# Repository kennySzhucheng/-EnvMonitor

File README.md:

# EnvMonitor — 智能环境监测站

> STM32F103C8T6 + FreeRTOS + ESP8266 桌面环境监测终端 | 练习项目

一个从零开始搭建的嵌入式 IoT 项目：裸机固件 → FreeRTOS 重构 → KiCad 画板 → 嘉立创打样，走完嵌入式产品全流程。

---

## 📸 实物展示

> ⏳ PCB 已下单，等待到货焊接后补图。

---

## ✨ 功能

| 模块 | 作用 |
|------|------|
| 🌡️ **DHT22** | 温湿度传感器，单总线(1-Wire)通信，精度 ±0.5°C / ±2%RH，挂在 PA0 上 |
| ☀️ **BH1750** | 环境光强度传感器，I²C 接口，0~65535 lux 量程，和 OLED 共用 PB6/PB7 |
| 📏 **HC-SR04** | 超声波测距模块，探测前方物体距离，用于"有人靠近"检测，PB0 发触发信号、PB1 输入捕获回波 |
| 🖥️ **OLED SSD1306** | 0.96 寸 I²C 显示屏，5 页菜单循环切换(温湿度/光照/距离/WiFi/系统信息) |
| 📡 **ESP8266-01S** | WiFi 模块，通过 UART1(PA9/PA10) 走 AT 指令，HTTP GET 方式每 60s 上传一次 ThingSpeak |
| 🚨 **三色 LED** | 红色(高温>35°C)、黄色(湿度<30%)、绿色(有人靠近<30cm)，分别接 PB12/13/14 |
| 🔔 **蜂鸣器** | 5V 有源模块，出现报警条件时由 BuzzerTask 队列驱动蜂鸣 |
| 🎛️ **三按键** | KEY1 页面切换 / KEY2 确认 / KEY3 返回，PA4/5/6，消抖电容 + 10kΩ 外部上拉 |
| ⏱️ **FreeRTOS** | 6 个任务抢占式调度，3 个互斥量保护共享资源，2 条队列做任务间通信 |
| 🛡️ **自定义 PCB** | KiCad 10 设计，80×60mm 双面板，全插件 27 元件，双面 GND 铺铜 |

---

## 🧱 硬件架构

```
                    ┌──────────────────────────────────┐
                    │        STM32F103C8T6 (72MHz)     │
                    │           Blue Pill 核心板         │
                    │                                  │
    DHT22 ──────────┤ PA0 (1-Wire)                     │
    KEY1~3 ─────────┤ PA4/PA5/PA6 (GPIO Input)        │
    ESP8266 ────────┤ PA9/PA10 (USART1, 115200bps)     │
    HC-SR04 ────────┤ PB0(Trig) / PB1(Echo, TIM3_CH4) │
    OLED+BH1750 ────┤ PB6/PB7 (I2C1, 共用总线)          │
    LED_R/Y/G ──────┤ PB12/PB13/PB14 (GPIO Output)     │
    Buzzer ─────────┤ PB15 (GPIO Output, 直连模块IO)    │
                    └──────────────────────────────────┘

    电源: USB 5V → Blue Pill → AMS1117 → 3.3V（全板供电来自 USB）
```

---

## 📐 引脚分配

| 引脚 | 外设 | 功能 |
|------|------|------|
| PA0 | DHT22 | 1-Wire 单总线 |
| PA4/PA5/PA6 | KEY1/KEY2/KEY3 | 按键输入(10kΩ 上拉) |
| PA9/PA10 | ESP8266 | USART1 TX/RX |
| PB0 | HC-SR04 Trig | 触发信号 |
| PB1 | HC-SR04 Echo | TIM3_CH4 输入捕获 |
| PB6/PB7 | OLED + BH1750 | I2C1 SCL/SDA（共用总线） |
| PB12/PB13/PB14 | LED_R/Y/G | 报警指示灯 |
| PB15 | Buzzer | 有源蜂鸣器模块 IO |
| PA13/PA14 | SWDIO/SWCLK | ST-Link 调试（保留） |

---

## 🖥️ 软件架构

```
                    ┌───────────────┐
                    │   FreeRTOS    │
                    │  V10.3.1      │
                    ├───────┬───────┤
                    │ 互斥量 ×3     │  队列 ×2
                    │ I2C / Data   │  Button → Display
                    │ / UART       │  Alarm → Buzzer
                    └───────┴───────┘
                           │
    ┌──────────────────────┼──────────────────────┐
    │                      │                      │
┌───▼──────┐  ┌──────▼─────┐  ┌────────▼───────┐
│SensorTask│  │DisplayTask │  │  CloudTask      │
│ (5s)     │  │ (1s)       │  │  (60s)          │
│ Prio:3   │  │ Prio:2     │  │  Prio:1         │
│          │  │             │  │                 │
│ DHT22    │  │ OLED 5页   │  │ ESP8266 AT指令  │
│ BH1750   │  │ 菜单渲染    │  │ HTTP GET        │
│ HC-SR04  │  │             │  │ ThingSpeak ☁️   │
└──────────┘  └─────────────┘  └─────────────────┘

┌──────────┐  ┌──────────────┐  ┌──────────────┐
│AlarmTask │  │ BuzzerTask   │  │ ButtonTask    │
│ (500ms)  │  │ (事件驱动)    │  │ (20ms)        │
│ Prio:3   │  │ Prio:2       │  │ Prio:2        │
│          │  │              │  │               │
│ 三级报警  │  │ xQueueReceive│  │ 状态机消抖     │
│ 阈值判断  │──▶ 阻塞等待     │  │ 队列发送事件   │
└──────────┘  └──────────────┘  └──────────────┘
```

**任务优先级原则：** 采集 > 报警 > 显示 = 按键 = 蜂鸣 > 上云

---

## 📦 物料清单 (BOM)

### PCB 焊接件（27个）

| 类型 | 规格 | 数量 | 位号 |
|------|------|------|------|
| 排母 | 1×20P 2.54mm | 2 | H1, H2 |
| 排针 | 1×4P 2.54mm | 3 | J2, J3, J4 |
| 排针 | 2×4P 2.54mm | 1 | J5 |
| 排针 | 1×3P 2.54mm | 1 | LS1 |
| 电阻 | 330Ω 1/4W | 3 | R10, R11, R12 |
| 电阻 | 4.7kΩ 1/4W | 3 | R4, R5, R6 |
| 电阻 | 10kΩ 1/4W | 3 | R7, R8, R9 |
| 瓷片电容 | 100nF (104) | 3 | C18, C19, C20 |
| 电解电容 | 100µF/10V | 2 | C21, C22 |
| LED 3mm | 红/黄/绿 | 3 | D2, D3, D4 |
| 轻触开关 | 6×6mm | 3 | SW2, SW3, SW4 |

### 外接模块（7个）

| 模块 | 数量 |
|------|------|
| STM32F103C8T6 Blue Pill | 1 |
| DHT22 温湿度传感器 | 1 |
| GY-302 光照 (BH1750) | 1 |
| OLED 0.96" SSD1306 | 1 |
| HC-SR04 超声波 | 1 |
| ESP8266-01S WiFi | 1 |
| 5V 有源蜂鸣器模块 | 1 |

> 💰 全部物料实际花费约 **90 元**（含 PCB 打样 20 元 + 模块 51 元 + 分立元件 13 元 + 工具 5 元）。完整清单见 `hardware/pcb/EnvMonitor/BOM_EnvMonitor.md`

---

## 🔧 开发环境

| 工具 | 用途 |
|------|------|
| **Keil MDK5** | 固件编译/烧录 |
| **STM32CubeMX** | 引脚配置 + HAL 代码生成 |
| **STM32CubeF1 V1.8.7** | HAL 库 + FreeRTOS 源码 |
| **ST-Link V2** | 调试/烧录器 |
| **KiCad 10.0** | 原理图 + PCB 设计 |
| **ThingSpeak** | IoT 数据可视化云平台 |

### 编译

1. 用 CubeMX 打开 `EnvMonitor.ioc` 重新生成代码（如需要）
2. `EnvMonitor\MDK-ARM\EnvMonitor.uvprojx` → Keil 打开
3. 确认 Include Paths 包含：`Drivers/*`、`App/`、`FreeRTOS/include`、`FreeRTOS/portable/RVDS/ARM_CM3`
4. Build (F7) → 0 Error → Download (F8)

### ThingSpeak 配置

1. 注册 https://thingspeak.com → Create Channel → 4 Fields
2. 将 Write API Key 填入 `esp8266.h` 中的 `THINGSPEAK_API_KEY`
3. 修改 WiFi 账号密码：`esp8266.h` → `WIFI_SSID` / `WIFI_PASS`

---

## 📂 项目结构

```
EnvMonitor/
├── firmware/               ← 固件源码（裸机版 + FreeRTOS版）
│   ├── Core/               HAL 配置 + main.c
│   ├── Drivers/            8 个外设驱动
│   │   ├── DHT22/          温湿度传感器
│   │   ├── BH1750/         光照传感器
│   │   ├── HC_SR04/        超声波测距
│   │   ├── OLED/           SSD1306 显示 + 字库
│   │   ├── ESP8266/        WiFi + ThingSpeak
│   │   ├── LED/            三色指示灯
│   │   ├── Button/         按键(状态机消抖)
│   │   └── Buzzer/         蜂鸣器
│   └── App/                应用层(状态机/菜单/报警)
│
├── EnvMonitor/             ← Keil + CubeMX 工程
│   ├── Core/               CubeMX 生成(含 main.c)
│   ├── Drivers/            同上 8 驱动 + ST HAL 库
│   ├── App/                6 个 FreeRTOS 任务 + task_shared
│   ├── MDK-ARM/            Keil 工程文件
│   └── EnvMonitor.ioc      CubeMX 项目
│
├── hardware/pcb/EnvMonitor/ ← KiCad PCB 设计
│   ├── EnvMonitor.kicad_*  工程文件
│   ├── BOM_EnvMonitor.md   完整物料清单
│   ├── EnvMonitor_Gerber_Full.zip  嘉立创打样包
│   ├── gerber/             Gerber 源文件(11层)
│   └── analysis/           出厂分析报告
│
└── docs/                   项目文档
    ├── 接线图.md            引脚分配表
    ├── 开发日志.md           设计决策 + 踩坑记录
    ├── 原理图讲解.md
    ├── KiCad入门讲解.md
    ├── PCB布局布线入门.md
    └── FreeRTOS入门讲解.md
```

---

## 📝 开发历程

| 阶段 | 内容 | 状态 |
|------|------|------|
| P0 | 项目规划 + 器件采购 | ✅ |
| P1-P6 | 裸机固件：8 驱动 + 5 页菜单 + 报警 + 上云 | ✅ |
| P7 | FreeRTOS 6 任务重构 | ✅ |
| P8 | KiCad 原理图 → 布局 → 布线 → DRC → Gerber | ✅ |
| P9 | 嘉立创打样 → 焊接 → 联调 → 发布 | 🔄 |

### 🔥 关键问题与解决

> 完整记录见 [`docs/开发日志.md`](docs/开发日志.md)

| # | 问题 | 根因 | 解决 |
|---|------|------|------|
| 1 | Keil 编译 `cannot open oled.h` | **循环包含**：`main.h` ↔ 驱动 `.h` 互相 include | 驱动 `.h` 改用 `stm32f1xx_hal.h`，`.c` 先 include `main.h` |
| 2 | FreeRTOS 链接 4 个 Undefined | 调试钩子未实现，V10.x 默认开启 | 关闭 MallocFailedHook / StackOverflowHook / StaticAllocation |
| 3 | KiCad 标签放空白处 | 标签必须附着在导线上，否则 = 独立网络 | 标签放在导线段上，高亮确认后放下 |
| 4 | 按键消抖电路出错 | R/C/SW/MCU 未在同一节点，MCU 脚孤悬 | 四者交汇一点，SW 另一脚 → GND |
| 5 | 14 个元件 PCB 导入失败 | 封装名缺脚距后缀（如 `_P2.54mm_Vertical`） | 编辑 `.kicad_sch` 批量替换封装名 |
| 6 | 蜂鸣器方案紧急变更 | 实物 3 脚模块 vs 原理图 2 脚+NPN 驱动 | 换 3 脚排针，删 Q1/R13/R14/D5，MCU 直连 |
| 7 | GND 铺铜 DRC 仍报未连接 | 铺铜只创建轮廓，没填充 | 按 **B** 键填充所有区域 |
| 8 | Keil 缺 `configUSE_16_BIT_TICKS` | FreeRTOS V10.x 新增必选宏 | `FreeRTOSConfig.h` 补定义 |
| 9 | 面包板测试失败，跳过直接上 PCB | STM32 内部上拉 ~40kΩ 太弱，面包板寄生干扰导致引脚浮空、按键读值随机跳变 | 外部 10kΩ 上拉 + PCB 实体焊点可彻底解决，不在面包板上浪费时间 |

### 💡 设计决策

| 决策 | 选择 | 理由 |
|------|------|------|
| RTOS | FreeRTOS 原生 API | 不依赖 CMSIS-RTOS 封装，社区资源多 |
| WiFi | ESP8266 AT 指令 + HTTP GET | ThingSpeak 原生支持，无需 MQTT broker |
| PCB | 全插件 THT + 模块化 | 新手可焊，Blue Pill 已有电路不重复画 |
| EDA | KiCad 10.0 | 开源免费，S-expression 格式透明 |
| I2C | OLED + BH1750 同总线 | 地址不同(0x3C/0x46)，不冲突，省 GPIO |

### 📚 学习历程

这个项目最大的收获不是做出来一个东西，而是 **5 天里从零啃下了 4 块硬骨头**：

| 技能 | 项目前 | 项目后 |
|------|--------|--------|
| **STM32 开发方式** | 只会标准库，没碰过 HAL | CubeMX 配置 + HAL 库驱动开发，理解句柄/初始化回调 |
| **FreeRTOS** | 完全不了解 | 6 任务抢占式调度，互斥量/队列/软件定时器，SysTick 三分天下 |
| **PCB 设计** | 零基础，没画过板 | KiCad 10.0 原理图→封装→布局→布线→铺铜→DRC→Gerber 全流程 |
| **项目工程化** | 单文件裸机循环 | 三层架构(Drivers/App/Core)，Git 版本控制，README 文档规范 |

> 💡 KiCad 入门借助了 Claude Code 的 KiCad Skill 辅助分析，但具体画板——元件摆放、走线、铺铜——还是得自己动手一刀一刀画，其实我以为可以让ai帮我解决排线问题，实则搞半天还是得自己来而且第一次画确实特别乱，没有经验，更改了很多遍

---

## 📄 许可

MIT License

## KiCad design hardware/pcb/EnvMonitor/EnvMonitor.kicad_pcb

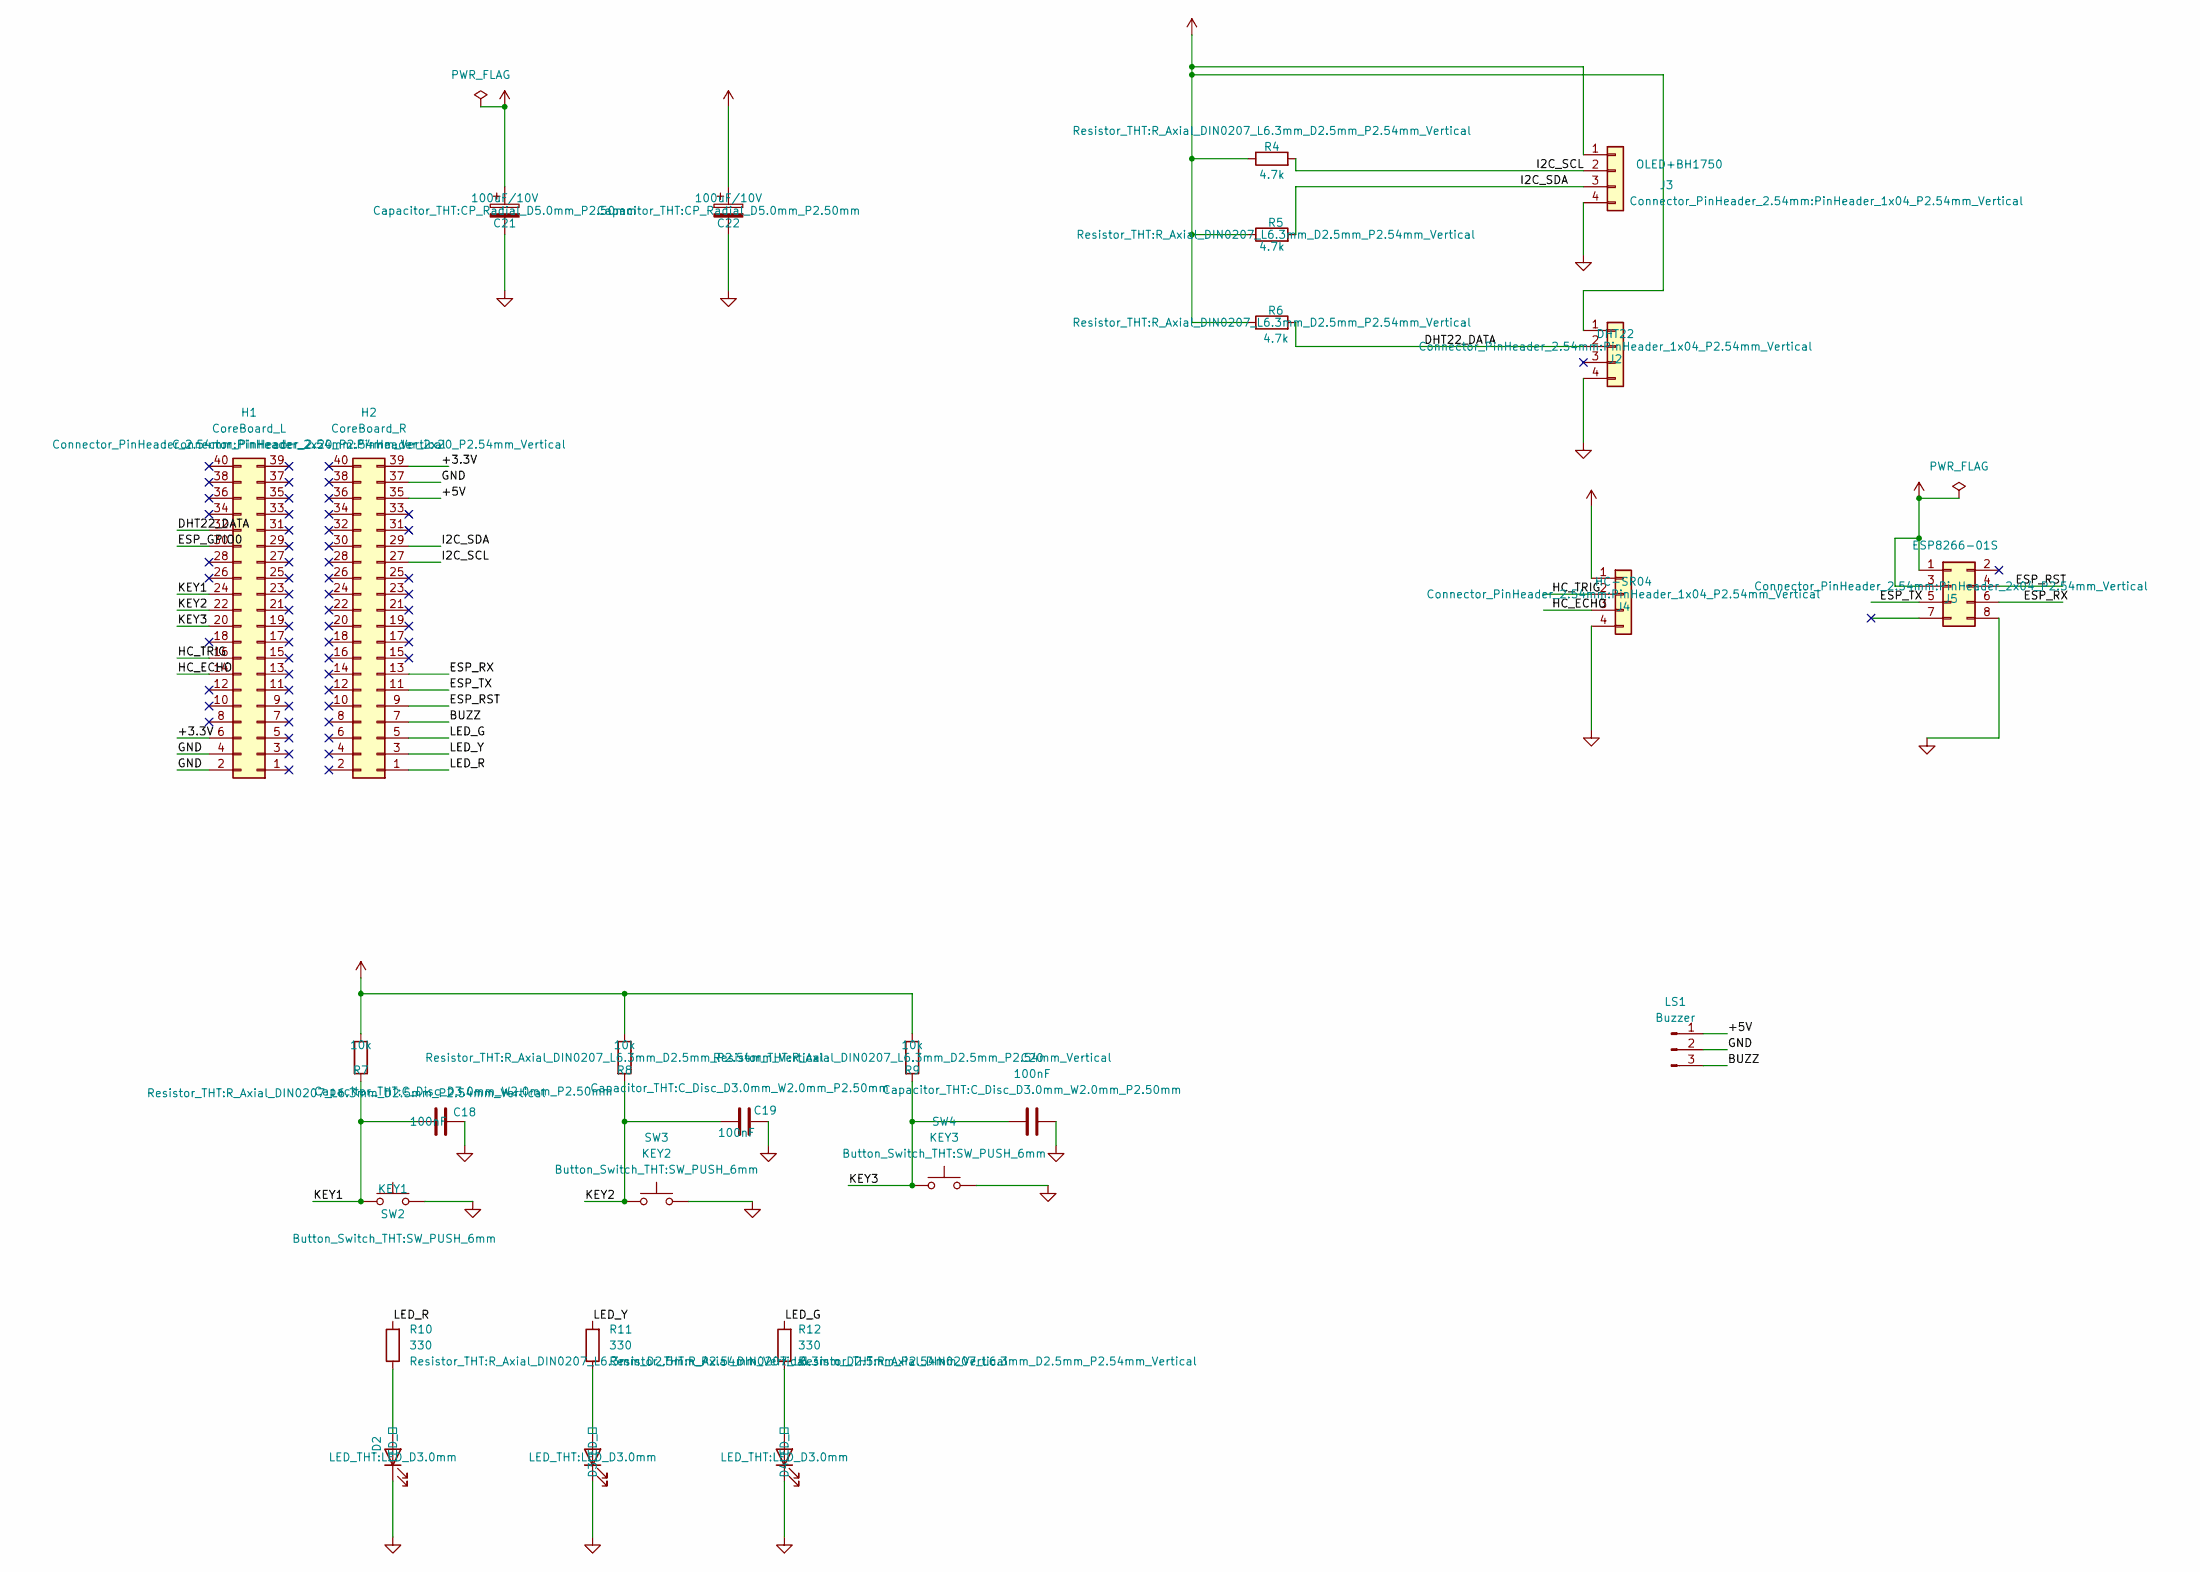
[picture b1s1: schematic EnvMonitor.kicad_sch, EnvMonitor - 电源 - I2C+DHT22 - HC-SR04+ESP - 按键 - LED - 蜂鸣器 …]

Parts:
C18, C19, C20: 100nF; C_Disc_D3.0mm_W2.0mm_P2.50mm
C21, C22: 100uF/10V; CP_Radial_D5.0mm_P2.50mm
D2: LED_红; LED_D3.0mm
D3: LED_黄; LED_D3.0mm
D4: LED_绿; LED_D3.0mm
H1: CoreBoard_L; PinHeader_2x20_P2.54mm_Vertical
H2: CoreBoard_R; PinHeader_2x20_P2.54mm_Vertical
J2: DHT22; PinHeader_1x04_P2.54mm_Vertical
J3: OLED+BH1750; PinHeader_1x04_P2.54mm_Vertical
J4: HC-SR04; PinHeader_1x04_P2.54mm_Vertical
J5: ESP8266-01S; PinHeader_2x04_P2.54mm_Vertical
LS1: Buzzer; PinHeader_1x03_P2.54mm_Vertical
R4, R5, R6: 4.7k; R_Axial_DIN0207_L6.3mm_D2.5mm_P2.54mm_Vertical
R7, R8, R9: 10k; R_Axial_DIN0207_L6.3mm_D2.5mm_P2.54mm_Vertical
R10, R11, R12: 330; R_Axial_DIN0207_L6.3mm_D2.5mm_P2.54mm_Vertical
SW2: KEY1; SW_PUSH_6mm
SW3: KEY2; SW_PUSH_6mm
SW4: KEY3; SW_PUSH_6mm

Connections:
+3.3V: C22.1, H1.6, H2.39, J2.1, J3.1, J5.1, J5.3, R4.1, R5.1, R6.1, R7.1, R8.1, R9.1
+5V: C21.1, H2.35, J4.1, LS1.1
/BUZZ: H2.7, LS1.3
/DHT22_DATA: H1.32, J2.2, R6.2
/ESP_GPIO0: H1.30
/ESP_RST: H2.9, J5.4
/ESP_RX: H2.13, J5.6
/ESP_TX: H2.11, J5.5
/HC_ECHO: H1.14, J4.3
/HC_TRIG: H1.16, J4.2
/I2C_SCL: H2.27, J3.2, R4.2
/I2C_SDA: H2.29, J3.3, R5.2
/KEY1: C18.1, H1.24, R7.2, SW2.1
/KEY2: C19.1, H1.22, R8.2, SW3.1
/KEY3: C20.1, H1.20, R9.2, SW4.1
/LED_G: H2.5, R12.2
/LED_R: H2.1, R10.2
/LED_Y: H2.3, R11.2
GND: C18.2, C19.2, C20.2, C21.2, C22.2, D2.1 (K), D3.1 (K), D4.1 (K), H1.2, H1.4, H2.37, J2.4, J3.4, J4.4, J5.8, LS1.2, SW2.2, SW3.2, SW4.2
unnamed: D2.2 (A), R10.1
unnamed: D3.2 (A), R11.1
unnamed: D4.2 (A), R12.1

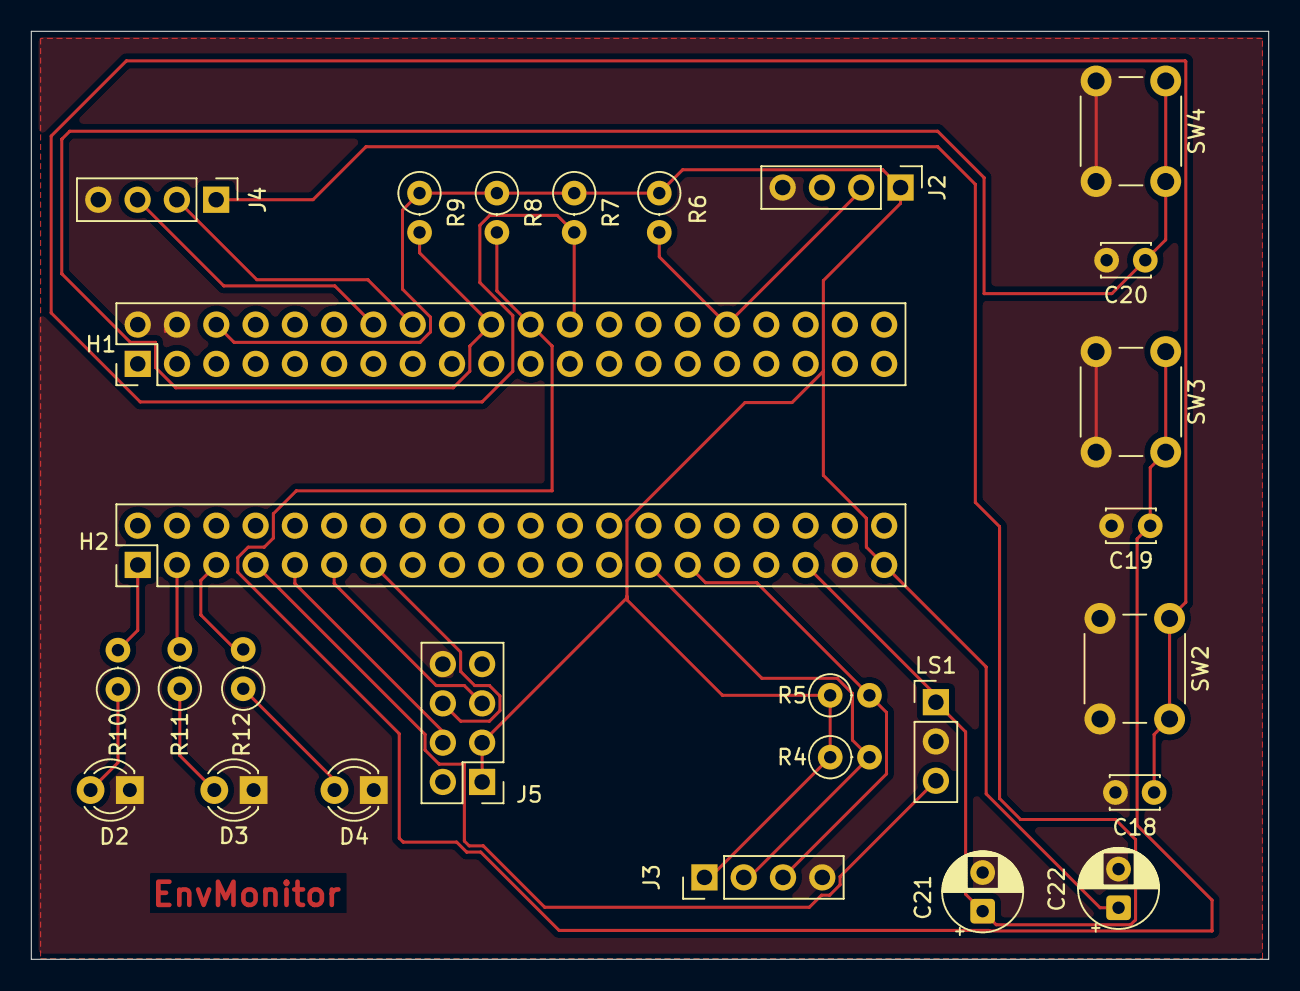
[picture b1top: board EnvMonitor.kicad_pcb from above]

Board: 2 copper layers, 80.0 x 60.0 mm, 27 parts (0 on the bottom side), 21 nets.

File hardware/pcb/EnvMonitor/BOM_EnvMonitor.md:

# 📋 EnvMonitor BOM 物料清单

> 板名：EnvMonitor | 主控：STM32F103C8T6 | 板尺寸：80×60mm | 层数：2层

---

## 一、PCB 焊接件（27 个）

### 🔌 连接器 (Connectors)

| 位号 | 数量 | 参数 | 封装/规格 |
|------|------|------|-----------|
| H1, H2 | 2 | Blue Pill 排母 | 1×20P 排母 2.54mm（需掰断使用） |
| J2 | 1 | DHT22 接口 | 1×4P 排针 2.54mm 直插 |
| J3 | 1 | OLED + BH1750 接口 | 1×4P 排针 2.54mm 直插（共用 I2C） |
| J4 | 1 | HC-SR04 接口 | 1×4P 排针 2.54mm 直插 |
| J5 | 1 | ESP8266-01S 接口 | 2×4P 排针 2.54mm 直插 |
| LS1 | 1 | 蜂鸣器接口 | 1×3P 排针 2.54mm 直插 |

### ⚡ 电阻 (Resistors) — 1/4W 金属膜

| 位号 | 数量 | 阻值 | 色环 | 用途 |
|------|------|------|------|------|
| R10, R11, R12 | 3 | **330Ω** | 橙橙棕金 | LED 限流 (D2/D3/D4) |
| R4, R5, R6 | 3 | **4.7kΩ** | 黄紫红金 | I2C 上拉 (OLED+BH1750) |
| R7, R8, R9 | 3 | **10kΩ** | 棕黑橙金 | 按键上拉 (SW2/SW3/SW4) |

### 🔵 电容 (Capacitors)

| 位号 | 数量 | 参数 | 封装 | 用途 |
|------|------|------|------|------|
| C18, C19, C20 | 3 | **100nF (104)** | 瓷片电容 2.54mm 脚距 | 按键消抖 |
| C21 | 1 | **100µF / 10V** | 电解电容 D5.0mm 脚距2.54mm | 3.3V 滤波 |
| C22 | 1 | **100µF / 10V** | 电解电容 D5.0mm 脚距2.54mm | 5V 滤波 |

### 💡 LED — 3mm 直插

| 位号 | 数量 | 颜色 | 用途 |
|------|------|------|------|
| D2 | 1 | **红色** | 高温报警指示 |
| D3 | 1 | **黄色** | 湿度低报警指示 |
| D4 | 1 | **绿色** | 靠近检测指示 |

### 🔘 按键

| 位号 | 数量 | 规格 | 用途 |
|------|------|------|------|
| SW2, SW3, SW4 | 3 | 6×6×4.3mm 轻触开关 | KEY1(页面切换), KEY2(确认), KEY3(返回) |

---

## 二、外接模块（7 个）— 通过排针/排母连接

| 序号 | 模块 | 数量 | 接口 | 连接到 |
|------|------|------|------|--------|
| 1 | **Blue Pill (STM32F103C8T6)** | 1 | 2×20P 排针 | H1 + H2 排母 |
| 2 | **DHT22 温湿度传感器** | 1 | 4Pin 排母 | J2 (1×4P) |
| 3 | **GY-302 光照 (BH1750)** | 1 | I²C 排针 | J3 与 OLED 共用 I²C |
| 4 | **OLED 0.96" SSD1306** | 1 | I²C 4Pin | J3 (1×4P) |
| 5 | **HC-SR04 超声波** | 1 | 4Pin 排母 | J4 (1×4P) |
| 6 | **ESP8266-01S WiFi** | 1 | 2×4P 排母 | J5 (2×4P) |
| 7 | **5V 有源蜂鸣器模块** | 1 | 3Pin 排母 | LS1 (1×3P) |

---

## 三、工具/烧录

| 物品 | 数量 | 用途 |
|------|------|------|
| ST-Link V2 下载器 | 1 | 固件烧录/调试 |
| USB 转 TTL (HW-597) | 1 | ESP8266 调试/AT 固件烧录 |
| Micro USB 线 | 1 | Blue Pill 供电 |

---

## 四、汇总

### PCB 焊接件

| 类别 | 种类 | 总数量 |
|------|------|--------|
| 排针/排母 | 6 种 | 7 个 |
| 电阻 | 3 种阻值 | 9 个 |
| 瓷片电容 | 1 种 | 3 个 |
| 电解电容 | 1 种 | 2 个 |
| LED | 3 种颜色 | 3 个 |
| 轻触开关 | 1 种 | 3 个 |
| **合计** | **11 种规格** | **27 个焊接点** |

### 全部（含模块）

| 项目 | 数量 |
|------|------|
| PCB 焊接件 | 27 个 |
| 外接模块 | 7 个 |
| 工具 | 3 个 |
| **总计** | **37 件** |

---

> 📝 **BOM 生成时间**: 2026-07-20
> 📝 **注意**: 电解电容(C21/C22)和 100nF 瓷片电容(C18/C19/C20) 为之前标记的「待补买」项，打样前需确认已购买。

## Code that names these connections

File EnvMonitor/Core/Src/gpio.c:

/* USER CODE BEGIN Header */
/**
  ******************************************************************************
  * @file    gpio.c
  * @brief   This file provides code for the configuration
  *          of all used GPIO pins.
  ******************************************************************************
  * @attention
  *
  * Copyright (c) 2026 STMicroelectronics.
  * All rights reserved.
  *
  * This software is licensed under terms that can be found in the LICENSE file
  * in the root directory of this software component.
  * If no LICENSE file comes with this software, it is provided AS-IS.
  *
  ******************************************************************************
  */
/* USER CODE END Header */

/* Includes ------------------------------------------------------------------*/
#include "gpio.h"

/* USER CODE BEGIN 0 */

/* USER CODE END 0 */

/*----------------------------------------------------------------------------*/
/* Configure GPIO                                                             */
/*----------------------------------------------------------------------------*/
/* USER CODE BEGIN 1 */

/* USER CODE END 1 */

/** Configure pins as
        * Analog
        * Input
        * Output
        * EVENT_OUT
        * EXTI
*/
void MX_GPIO_Init(void)
{

  GPIO_InitTypeDef GPIO_InitStruct = {0};

  /* GPIO Ports Clock Enable */
  __HAL_RCC_GPIOA_CLK_ENABLE();
  __HAL_RCC_GPIOB_CLK_ENABLE();

  /*--- 初始输出电平：全部拉低 ---*/
  HAL_GPIO_WritePin(GPIOA, DHT22_PIN, GPIO_PIN_SET);       /* DHT22总线空闲=高 */
  HAL_GPIO_WritePin(GPIOB, SR04_TRIG_PIN | LED_RED_PIN | LED_YELLOW_PIN
                          | LED_GREEN_PIN | BUZZER_PIN, GPIO_PIN_RESET);

  /*--- PA0: DHT22 数据线（开漏输出，模拟1-Wire双向） ---*/
  GPIO_InitStruct.Pin = DHT22_PIN;
  GPIO_InitStruct.Mode = GPIO_MODE_OUTPUT_OD;
  GPIO_InitStruct.Pull = GPIO_PULLUP;
  GPIO_InitStruct.Speed = GPIO_SPEED_FREQ_HIGH;
  HAL_GPIO_Init(GPIOA, &GPIO_InitStruct);

  /*--- PA4/PA5/PA6: 按键输入（内部上拉，按下为低） ---*/
  GPIO_InitStruct.Pin = KEY1_PIN | KEY2_PIN | KEY3_PIN;
  GPIO_InitStruct.Mode = GPIO_MODE_INPUT;
  GPIO_InitStruct.Pull = GPIO_PULLUP;
  HAL_GPIO_Init(GPIOA, &GPIO_InitStruct);

  /*--- PB0: HC-SR04 Trig 推挽输出 ---*/
  GPIO_InitStruct.Pin = SR04_TRIG_PIN;
  GPIO_InitStruct.Mode = GPIO_MODE_OUTPUT_PP;
  GPIO_InitStruct.Pull = GPIO_PULLDOWN;
  GPIO_InitStruct.Speed = GPIO_SPEED_FREQ_LOW;
  HAL_GPIO_Init(GPIOB, &GPIO_InitStruct);

  /*--- PB12/PB13/PB14: LED红黄绿 ---*/
  GPIO_InitStruct.Pin = LED_RED_PIN | LED_YELLOW_PIN | LED_GREEN_PIN;
  GPIO_InitStruct.Mode = GPIO_MODE_OUTPUT_PP;
  GPIO_InitStruct.Pull = GPIO_NOPULL;
  GPIO_InitStruct.Speed = GPIO_SPEED_FREQ_LOW;
  HAL_GPIO_Init(GPIOB, &GPIO_InitStruct);

  /*--- PB15: 蜂鸣器 ---*/
  GPIO_InitStruct.Pin = BUZZER_PIN;
  GPIO_InitStruct.Mode = GPIO_MODE_OUTPUT_PP;
  GPIO_InitStruct.Pull = GPIO_NOPULL;
  GPIO_InitStruct.Speed = GPIO_SPEED_FREQ_LOW;
  HAL_GPIO_Init(GPIOB, &GPIO_InitStruct);

}

/* USER CODE BEGIN 2 */

/* USER CODE END 2 */
